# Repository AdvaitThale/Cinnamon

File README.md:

# Cinnamon
An open-source operating system for embedded/IoT-based systems giving support to a wide range of microcontrollers. 
E-mail for Token access.

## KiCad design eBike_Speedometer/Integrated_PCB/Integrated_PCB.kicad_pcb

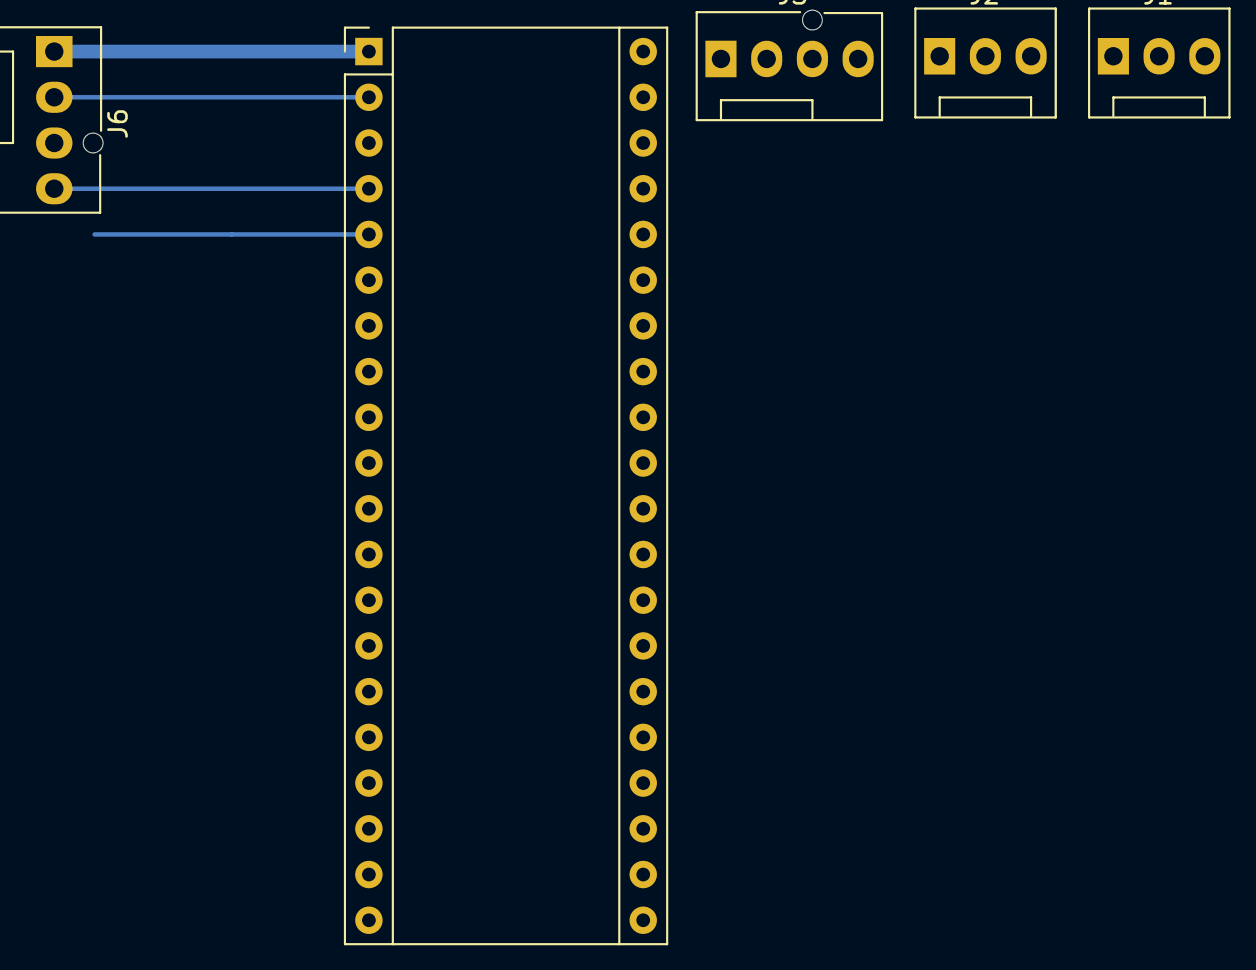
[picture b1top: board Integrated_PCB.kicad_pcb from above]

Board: 2 copper layers, 5 parts (0 on the bottom side), 4 nets.

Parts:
A1: Maple_Mini
J1, J2: Conn_01x03_Male; FanPinHeader_1x03_P2.54mm_Vertical
J3, J6: Conn_01x04_Female; FanPinHeader_1x04_P2.54mm_Vertical

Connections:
GND: A1.2 (GND), J6.2
SCL: A1.4 (SCL1/D15), J6.4
SDA: A1.5 (SDA1/D16), J6.3
VCC: A1.1 (VCC), J6.1

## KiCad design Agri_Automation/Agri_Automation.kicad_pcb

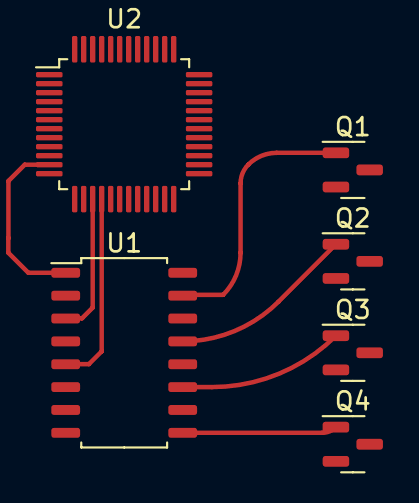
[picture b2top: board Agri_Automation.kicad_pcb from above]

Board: 2 copper layers, 6 parts (0 on the bottom side), 7 nets.

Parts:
Q1, Q2, Q3, Q4: MMBT3904; SOT-23
U1: TLP291-4; SOIC-16_4.55x10.3mm_P1.27mm
U2: STM32F103C8Tx; LQFP-48_7x7mm_P0.5mm

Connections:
unnamed: U1.1, U2.11 (PA1)
unnamed: U1.3, U2.15 (PA5)
unnamed: U1.5, U2.16 (PA6)
unnamed: Q4.1 (B), U1.9
unnamed: Q3.1 (B), U1.11
unnamed: Q2.1 (B), U1.13
unnamed: Q1.1 (B), U1.15

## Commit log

2024-01-26 _changelog (#1)
2024-01-26 _changelog (#2)
2024-03-10 _changelog (#3) - BLE_Mouse
2024-04-03 _changelog (#3)
2024-07-09 _changelog( #4)
2024-12-19 _changelog (#5)
2024-12-20 _changelog (#6)
2024-12-23 _changelog (#7)
2024-12-24 _changelog (#8)
2024-12-25 _changelog (#9)
2024-12-26 _changelog (#10)
2024-12-30 _changelog (#11)
2024-12-31 _changelog (#12)
2025-01-01 _changelog (#13)
2025-01-03 _changelog (#14)
2025-01-06 _changelog (#15)
2025-01-07 _changelog (#16)
2025-08-06 _chnagelog(#17)
